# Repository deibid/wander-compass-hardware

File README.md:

# wander-compass-hardware
 Wander Compass is a wearable that takes you to streets where you have never been before. This repository contains the Arduino app component and schematic files

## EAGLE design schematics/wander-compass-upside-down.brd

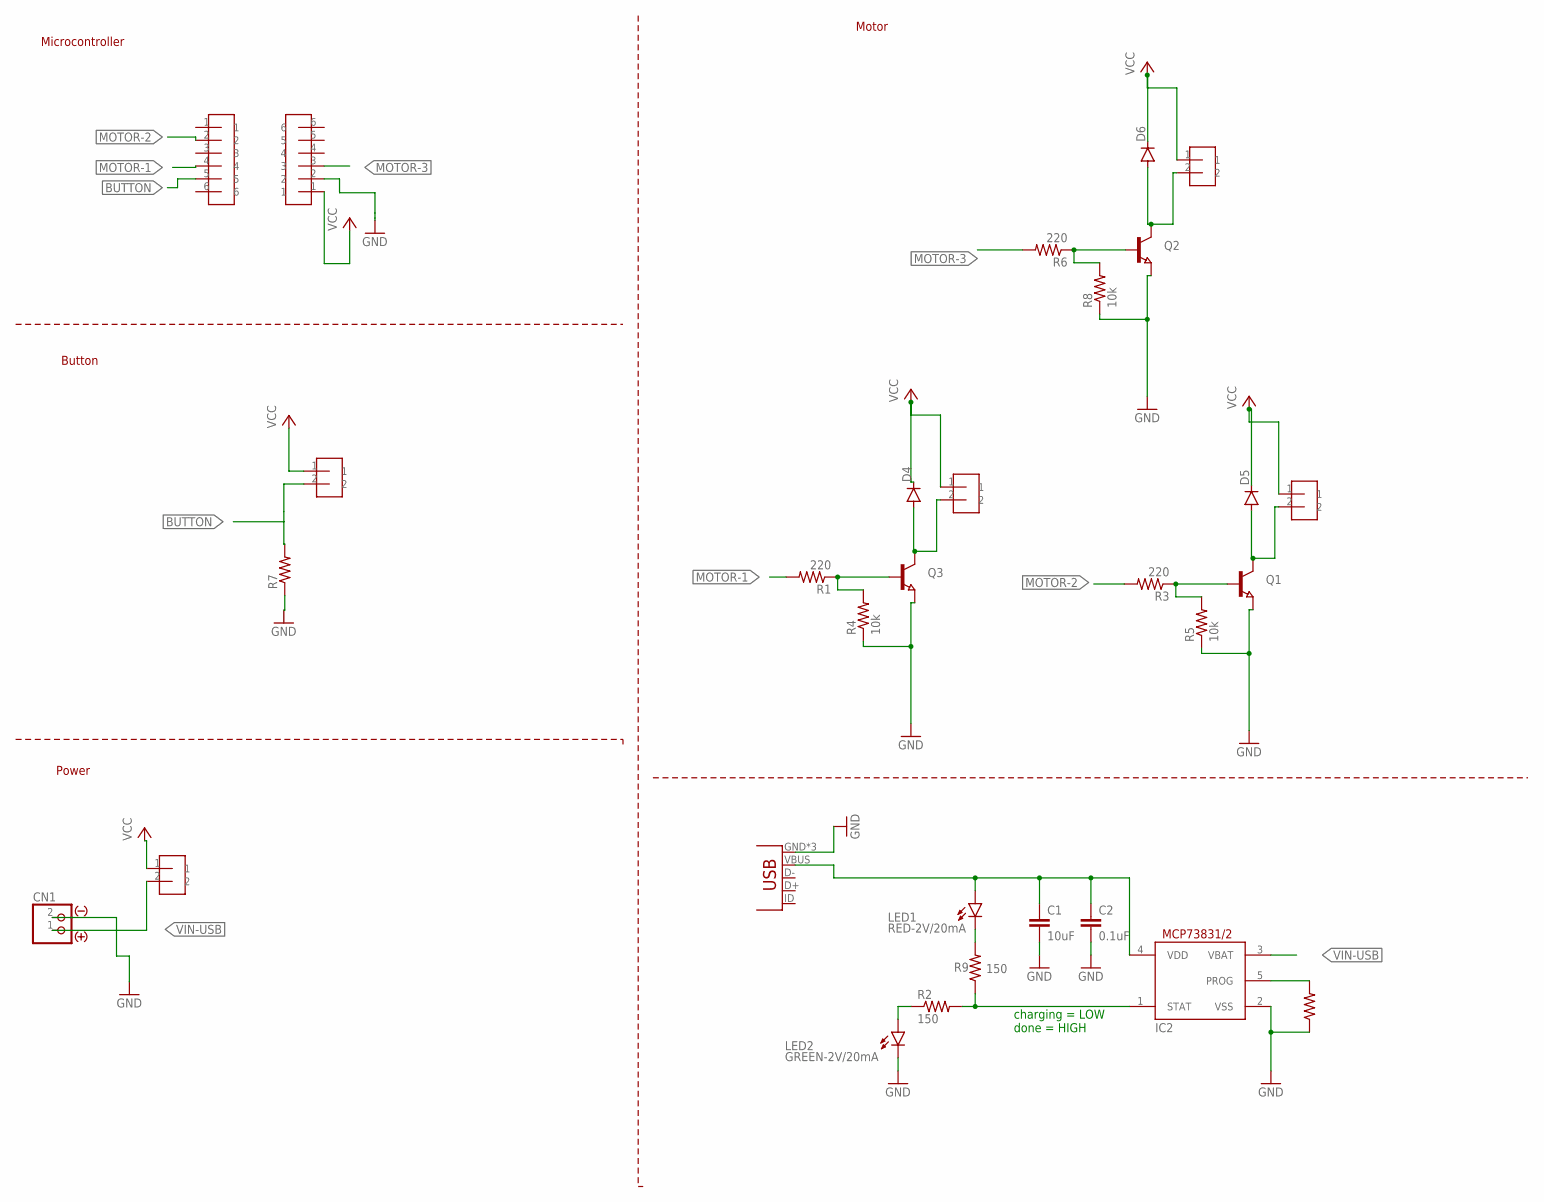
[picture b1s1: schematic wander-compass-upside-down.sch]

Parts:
C1: 10uF; 0805
C2: 0.1uF; 0805
CN1: JST_2PIN_BATTERY-SMT-HORIZ; JST-PH-2-SMT-RA
D4, D5, D6: DIODE-SOD523; SOD523
IC2: LIPO_CHARGER/OT; SOT23-5L
JP1: USB_CONN-10118192-0001LF; USB-MICROB
LED1: RED-2V/20mA; CHIP-LED0805
LED2: GREEN-2V/20mA; CHIP-LED0805
MOTOR-CENTER-HEADER: HEADER-2
MOTOR-RIGHT-HEADER: HEADER-2
MOTOR_LEFT_HEADER: HEADER-2
Q1, Q2, Q3: TRANSISTOR-NPN-SOT23; SOT23
R1, R3, R6: 220; 0603-RES
R2, R9: 150; 0805
R4, R5, R8: 10k; 0603-RES
R7: RESISTOR0603; 0603-RES
R10: 2k; 0805
U$1, U$7: HEADER-2
U$5, U$6: HEADER-6

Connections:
5V: C1.1, C2.1, IC2.4 (VDD), JP1.VBUS, LED1.A
BUTTON: R7.2, U$1.2, U$6.5
CURRENT-CONTROL: IC2.5 (PROG), R10.2
GND: C1.2, C2.2, CN1.2 (1), IC2.2 (VSS), JP1.GND, JP1.MT1 (GND), JP1.MT2 (GND), LED2.C, Q1.2 (E), Q2.2 (E), Q3.2 (E), R4.1, R5.1, R7.1, R8.1, R10.1, U$5.2
MOTOR-1: R1.2, U$6.4
MOTOR-2: R3.2, U$6.2
MOTOR-3: R6.2, U$5.3
unnamed: D4.A, MOTOR_LEFT_HEADER.2, Q3.3 (C)
unnamed: Q1.1 (B), R3.1, R5.2
unnamed: D5.A, MOTOR-CENTER-HEADER.2, Q1.3 (C)
unnamed: Q3.1 (B), R1.1, R4.2
unnamed: Q2.1 (B), R6.1, R8.2
unnamed: D6.A, MOTOR-RIGHT-HEADER.2, Q2.3 (C)
unnamed: LED1.C, R9.2
unnamed: LED2.A, R2.1
STATUS: IC2.1 (STAT), R2.2, R9.1
VCC: D4.C, D5.C, D6.C, MOTOR-CENTER-HEADER.1, MOTOR-RIGHT-HEADER.1, MOTOR_LEFT_HEADER.1, U$1.1, U$5.1, U$7.1
VIN-USB: CN1.1 (2), IC2.3 (VBAT), U$7.2

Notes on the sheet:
Motor
Microcontroller
Power
Button
charging = LOW done = HIGH

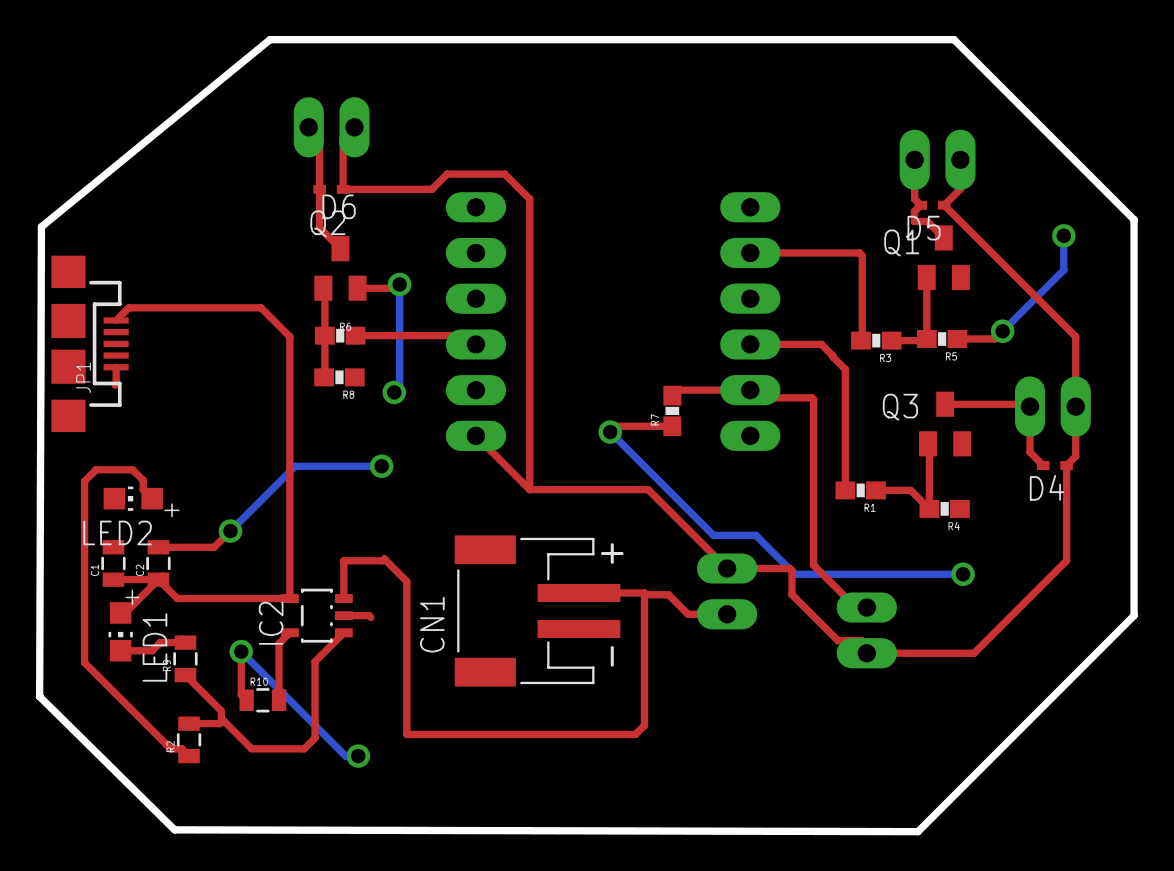
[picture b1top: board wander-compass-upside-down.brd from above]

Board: 2 copper layers, 60.8 x 44.0 mm, 30 parts (0 on the bottom side), 18 nets.

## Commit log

2019-05-05 Create LICENSE
2019-05-05 initial commit on separate repo
2019-05-05 added schematics v1.2
2019-05-12 changed pin decalration and remove unsused code
2019-05-16 tweaked motor feedback

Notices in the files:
parts and their libraries:
SparkFun-Aesthetics: Licensing: Creative Commons ShareAlike 4.0 International - https://creativecommons.org/licenses/by-sa/4.0
